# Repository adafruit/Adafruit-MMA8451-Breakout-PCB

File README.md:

## Adafruit MMA8451 Triple-Axis Accelerometer - ±2/4/8g @ 14-bit Breakout PCB
<a href="http://www.adafruit.com/products/2019"><br/>
Click here to purchase one from the Adafruit shop</a>

So many accelerometers and so little time! We've expanded our accelerometer selection even more with this high-precision and inexpensive MMA8451 Triple-Axis Accelerometer w/ 14-bit ADC. You can detect motion, tilt and basic orientation with a digital accelerometer - and the MMA8451 is a great accelerometer to start with. It has a wide usage range, from +-2g up to +-8g yet is easy to use with Arduino or another microcontroller

The MMA8451 is a miniature little accelerometer from Freescale, who are (by this point) masters at the accelerometer-design game. It's designed for use in phones, tablets, smart watches, and more, but works just as well in your Arduino project. Of the MMA8451/MMA8452/MMA8453 family, the MMA8451 is the most precise with a built in 14-bit ADC. The accelerometer also has built in tilt/orientation detection so it can tell you whether your project is being held in landscape or portrait mode, and whether it is tilted forward or back

PCB files for the Adafruit MMA8451 Breakout. The format is EagleCAD schematic and board layout
- https://www.adafruit.com/product/2019

### License

Adafruit invests time and resources providing this open source design, please support Adafruit and open-source hardware by purchasing products from [Adafruit](https://www.adafruit.com)!

All text above must be included in any redistribution

Designed by Limor Fried/Ladyada for Adafruit Industries.
Creative Commons Attribution/Share-Alike, all text above must be included in any redistribution. 
See license.txt for additional information.

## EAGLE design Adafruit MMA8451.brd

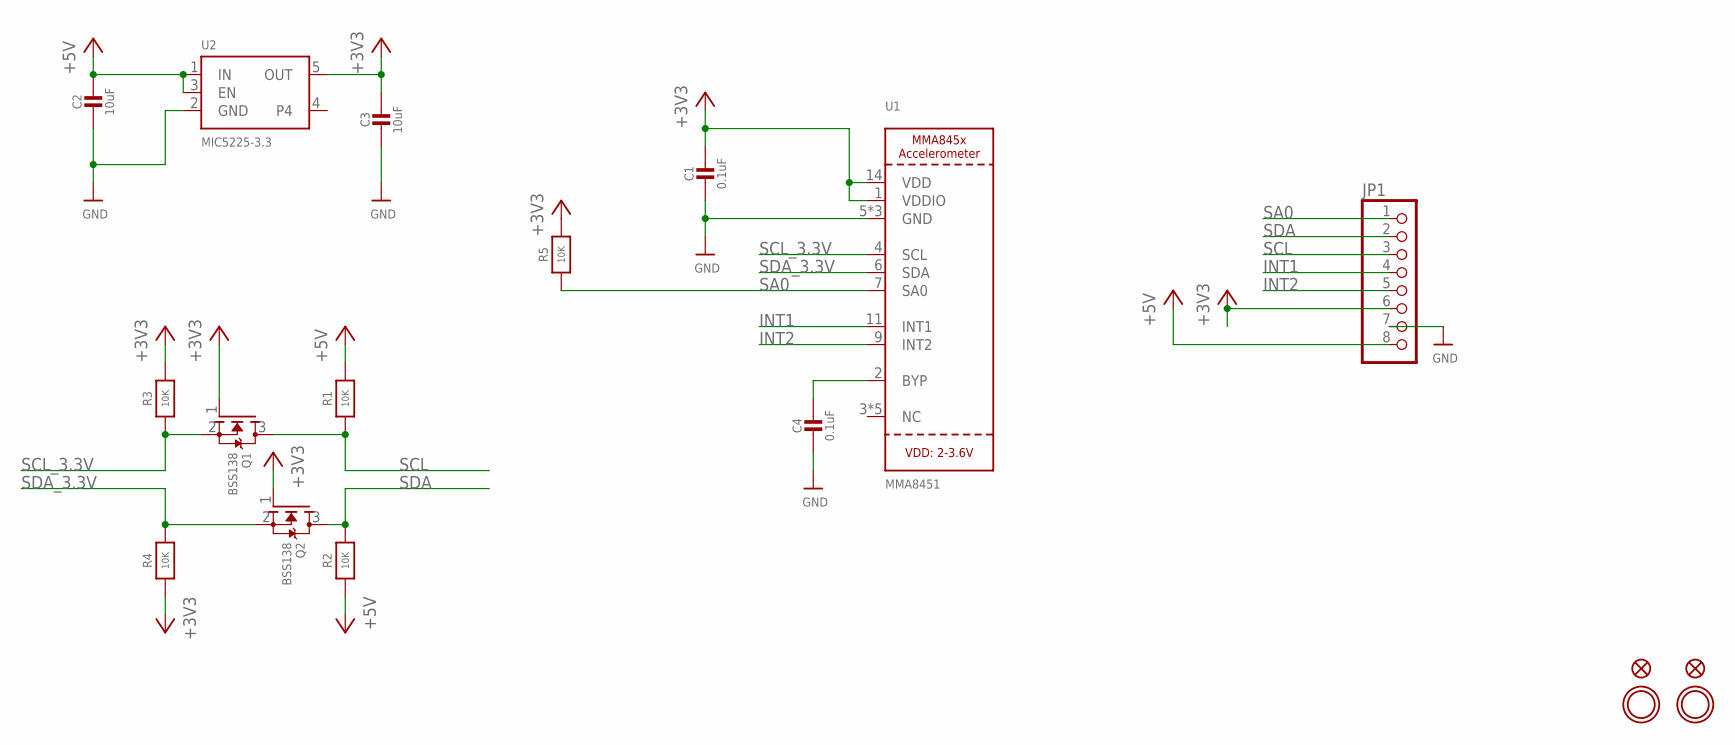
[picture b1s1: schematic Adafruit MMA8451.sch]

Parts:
C1: 0.1uF; 0805-NO
C2, C3: 10uF; 0805-NO
C4: 0.1uF; 0805_10MGAP
FID1, FID2: FIDUCIAL""; FIDUCIAL_1MM
JP1: HEADER-1X870MIL; 1X08_ROUND_70
Q1, Q2: BSS138; SOT23-WIDE
R1, R2, R3, R4, R5: 10K; 0805-NO
U1: MMA8451; MMA845X_QFN_16MM
U2: MIC5225-3.3; SOT23-5
U$3, U$6: MOUNTINGHOLE2.5; MOUNTINGHOLE_2.5_PLATED

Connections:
+3V3: C1.1, C3.1, JP1.6, Q1.1 (G), Q2.1 (G), R3.2, R4.1, R5.2, U1.1 (VDDIO), U1.14 (VDD), U2.5 (OUT)
GND: C1.2, C2.2, C3.2, C4.2, JP1.7, U1.5 (GND), U1.10 (GND), U1.12 (GND), U2.2 (GND)
INT1: JP1.4, U1.11 (INT1)
INT2: JP1.5, U1.9 (INT2)
unnamed: C4.1, U1.2 (BYP)
SA0: JP1.1, R5.1, U1.7 (SA0)
SCL: JP1.3, Q1.3 (D), R1.1
SCL_3.3V: Q1.2 (S), R3.1, U1.4 (SCL)
SDA: JP1.2, Q2.3 (D), R2.2
SDA_3.3V: Q2.2 (S), R4.2, U1.6 (SDA)
VIN: C2.1, JP1.8, R1.2, R2.1, U2.1 (IN), U2.3 (EN)

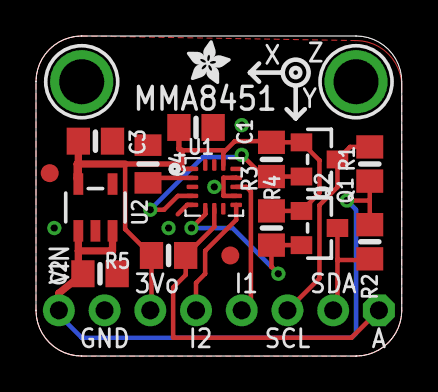
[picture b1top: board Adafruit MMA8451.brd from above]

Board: 2 copper layers, 20.3 x 17.8 mm, 19 parts (0 on the bottom side), 11 nets.

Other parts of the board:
U$10: ADAFRUIT_2.5MM

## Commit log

2016-08-15 init

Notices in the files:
parts and their libraries:
microbuilder: This work is placed in the public domain, and may be freely used for commercial and non-commercial work with the following conditions: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
